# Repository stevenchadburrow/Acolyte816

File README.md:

# Acolyte816

An Acolyte Computer using the W65C816S.

It runs at 12.5 MHz and has 1 MB of RAM.  Video output of 64-colors at 320x240 or monochrome at 640x240.  PS/2 Keyboard and Mouse, 2x Genesis Controllers, and 1-Voice Square wave audio output.

This is a ROM-less design, having 512 bytes of bootloader code in the PIC16F886 "spoon feeding" the '816 on power-up or reset.  After that the PIC controls the MicroSD Card to access up to 2GB of memory.

The Simulator is powered by gianlucag's 6502 emulator library, with Agumander's W65C02 edits.  The LICENSE.txt pertains to the "mos6502-Edit816.h" and "mos6502-Edit816.cpp" files only.

BODGES REQUIRED:  The 74AHCT245 connected to the PIC needs two changes: One, Pin 1 is no longer R/W but instead connected to +5V. Two, Pin 19 is connected to RC5.  Also, the FTDI USB 6-pin connector has RTS and DTS lines cut and no longer connected to RC4 and RC5.

A picture of the board after bodges.
<kbd>

</kbd>

Splash showing 64-colors and text display together.
<kbd>

</kbd>

Bootloader fallback monitor, when SDcard is not present.
<kbd>

</kbd>

Basic system monitor for read/write/execute.
<kbd>

</kbd>

Text editor with vertical scrolling, will be used as IDE for a higher level language soon.
<kbd>

</kbd>

First game for the system: Tetra!
<kbd>

</kbd>

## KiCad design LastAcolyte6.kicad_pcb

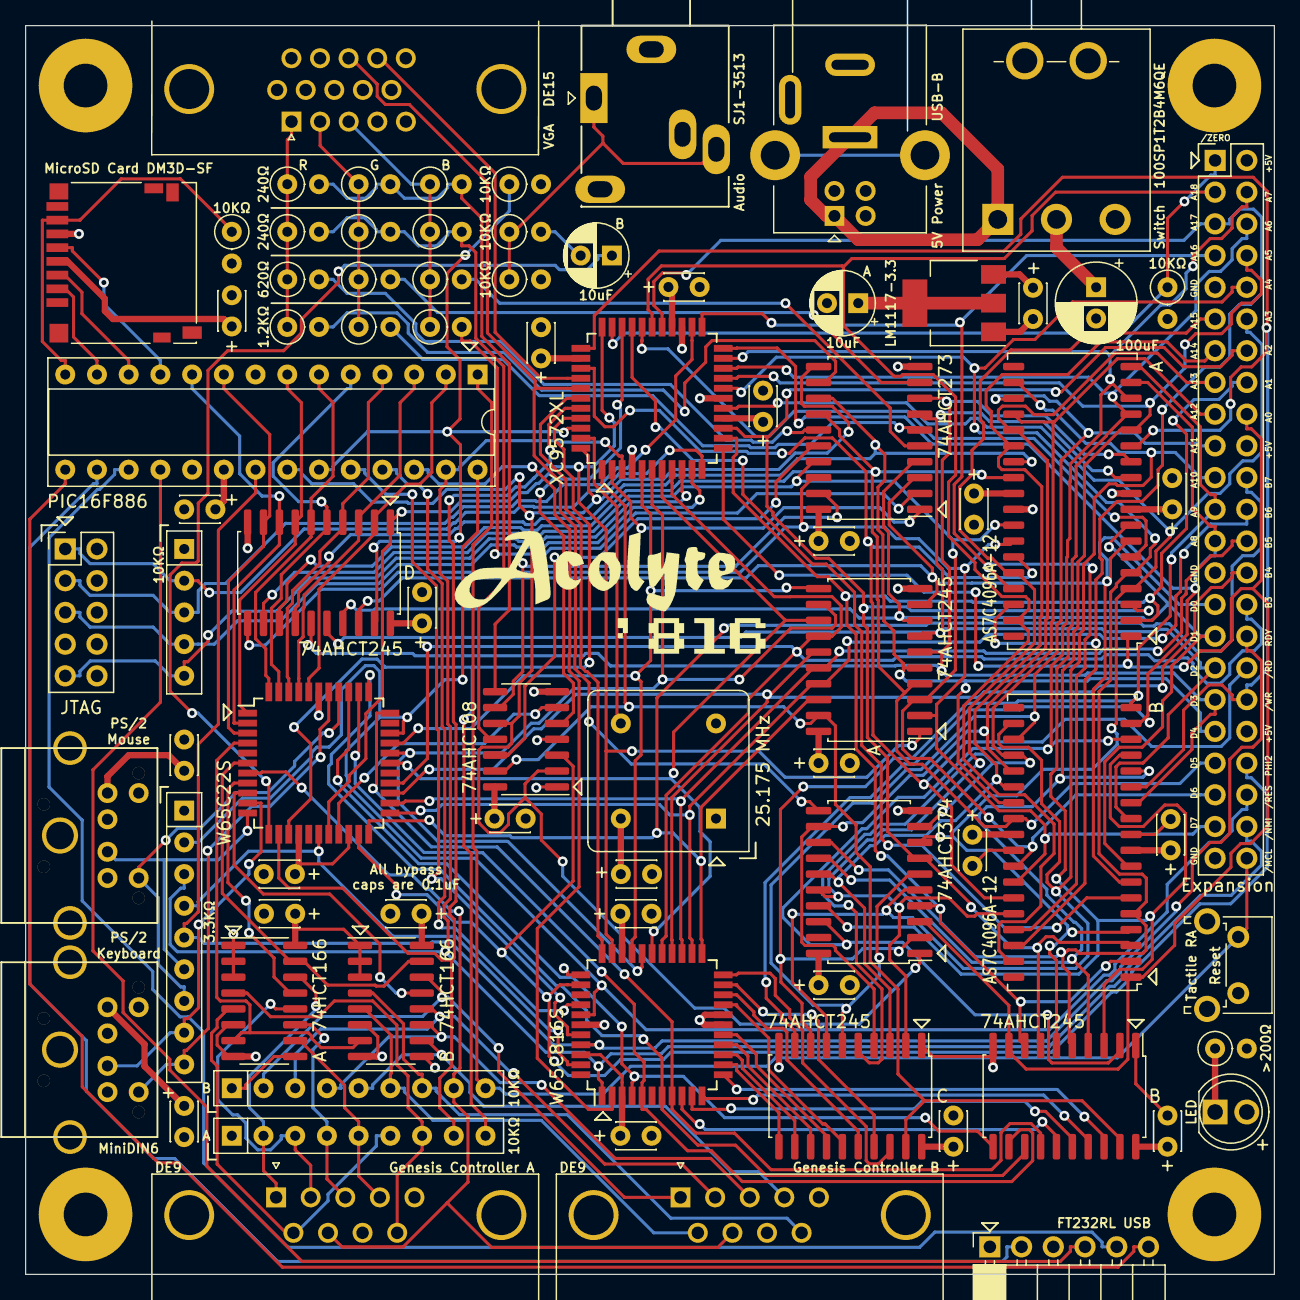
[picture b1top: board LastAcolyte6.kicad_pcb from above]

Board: 4 copper layers, 100.0 x 100.0 mm, 88 parts (1 on the bottom side), 140 nets.

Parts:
C1: C_Polarized_US; CP_Radial_D6.3mm_P2.50mm
C2, C4, C5, C6, C7, C8, C9, C10, C11, C12, C13, C14, C15, C16, C17, C18, C19, C20, C21, C23, C24, C25, C26, C27, C28: C_Small; C_Disc_D3.0mm_W2.0mm_P2.50mm
C3, C22: C_Polarized_Small_US; CP_Radial_D5.0mm_P2.50mm
D1: LED; CustomLED
G102: LOGO; Mystery
G1000: LOGO; AcolyteTitle
G1001: LOGO; Acolyte816
J1: Conn_02x23_Odd_Even; PinHeader_2x23_P2.54mm_Vertical
J2, J4: DE9_Plug; DSUB-9_Male_Horizontal_P2.77x2.84mm_EdgePinOffset7.70mm_Hou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
J3: Conn_02x05_Odd_Even; PinHeader_2x05_P2.54mm_Vertical
J5: DE15_Receptacle_HighDensity; DSUB-15-HD_Female_Horizontal_P2.29x2.54mm_VGA
J6: AudioJack3; BIGJack_3.5mm_Ledino_KB3SPRS_Horizontal
J7, J8: Mini-DIN-6; PS2_Din6
J9: Micro_SD_Card; microSD_HC_Hirose_DM3D-SF
J10: DualPower_USB_B; DualPowerSupply
J11: Conn_01x06; PinSocket_1x06_P2.54mm_Horizontal
R3, R4, R5, R7, R8, R9, R10, R11, R12, R13, R14, R15, R16, R18, R19, R20, R21, R22: R_US; R_Axial_DIN0207_L6.3mm_D2.5mm_P2.54mm_Vertical
RN1, RN2, RN3: R_Network08_US; R_Array_SIP9
RN4: R_Network04_US; R_Array_SIP5
SW1: SW_Push; SW_Tactile_SPST_Angled_PTS645Vx83-2LFS
SW2: SW_SPDT; SPDT-100SP1T2B4M6QE
TP1, TP2, TP3, TP4: TestPoint; ScrewHole-4-40
U1: XC9572VQ44; TQFP-44_10x10mm_P0.8mm
U2, U7: IS61C5128AL-10KLI; SOJ-36_10.16x23.49mm_P1.27mm
U3: LM1117MP-3.3; SOT-223-3_TabPin2
U4: W65C816SxQ; TQFP-44_10x10mm_P0.8mm
U5: W65C22SxQ; TQFP-44_10x10mm_P0.8mm
U6: 74AHCT273; SOIC-20-Adj_7.5x12.8mm_P1.27mm
U8, U9: 74HCT166; SOIC-16_3.9x9.9mm_P1.27mm
U10, U11, U15, U16: 74AHCT245; SOIC-20-Adj_7.5x12.8mm_P1.27mm
U12: 74AHCT08; SOIC-14_3.9x8.7mm_P1.27mm
U19: 74AHCT374; SOIC-20-Adj_7.5x12.8mm_P1.27mm
U21: PIC16F886-IP; DIP-28_W7.62mm_Socket
X1: CXO_DIP8; Oscillator_DIP-8

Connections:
+3.3V: C3.1, C5.2, C9.2, C13.2, C17.2, C21.2, J3.4, J9.4 (VDD), R3.2, RN4.1 (common), U1.15 (VCC-P21), U1.26 (VCCIO-P32), U1.35 (VCC-P41), U3.2 (VO), U21.20 (VDD)
+5V: C1.1, C2.2, C4.2, C6.2, C7.2, C8.2, C10.2, C11.2, C12.2, C14.2, C15.2, C16.2, C18.2, C19.2, C20.2, C23.2, C24.2, C25.2, C26.2, C27.2, C28.2, D1.2 (A), J1.2, J1.20, J1.38, J2.5, J4.5, J7.4, J8.4, RN1.1 (common), RN2.1 (common), RN3.1 (common), SW2.2 (B), U2.9 (VDD), U2.27 (VDD), U3.3 (VI), U4.3 (VDD), U4.31 (VDD), U4.34 (BE), U4.42 (~ABORT), U5.15 (VDD), U5.20 (CS1), U6.20 (VCC), U7.9 (VDD), U7.27 (VDD), U8.1 (Ds), U8.2 (A), U8.3 (B), U8.9 (Clr), U8.16 (VCC), U9.1 (Ds), U9.2 (A), U9.3 (B), U9.9 (Clr), U9.16 (VCC), U10.20 (VCC), U11.20 (VCC), U12.1, U12.4, U12.14 (VCC), U15.20 (VCC), U16.20 (VCC), U19.20 (VCC), X1.8 (Vcc)
/A0: J1.18, U1.12 (P18), U2.1 (A0), U7.1 (A0), U15.9 (A7), U19.3 (D0)
/A1: J1.16, U1.13 (P19), U2.2 (A1), U7.2 (A1), U15.8 (A6), U19.4 (D1)
/A2: J1.14, U1.14 (P20), U2.3 (A2), U7.3 (A2), U15.7 (A5), U19.7 (D2)
/A3: J1.12, U1.16 (P22), U2.4 (A3), U7.4 (A3), U15.6 (A4), U19.8 (D3)
/A4: J1.10, U1.18 (P24), U2.5 (A4), U7.5 (A4), U15.5 (A3), U19.13 (D4)
/A5: J1.8, U1.19 (P25), U2.14 (A5), U7.14 (A5), U15.4 (A2), U19.14 (D5)
/A6: J1.6, U1.20 (P26), U2.15 (A6), U7.15 (A6), U15.3 (A1), U19.17 (D6)
/A7: J1.4, U1.21 (P27), U2.16 (A7), U7.16 (A7), U15.2 (A0), U19.18 (D7)
/A8: J1.25, U1.22 (P28), U2.17 (A8), U7.17 (A8), U16.9 (A7)
/A9: J1.23, U2.18 (A9), U7.18 (A9), U16.8 (A6), U19.2 (O0)
/A10: J1.21, U2.20 (A10), U7.20 (A10), U16.7 (A5), U19.5 (O1)
/A11: J1.19, U2.21 (A11), U7.21 (A11), U16.6 (A4), U19.6 (O2)
/A12: J1.17, U2.22 (A12), U7.22 (A12), U16.5 (A3), U19.9 (O3)
/A13: J1.15, U2.23 (A13), U7.23 (A13), U16.4 (A2), U19.12 (O4)
/A14: J1.13, U2.24 (A14), U7.24 (A14), U16.3 (A1), U19.15 (O5)
/A15: J1.11, U2.32 (A15), U7.32 (A15), U16.2 (A0), U19.16 (O6)
/A16: J1.7, U1.23 (P29), U2.33 (A16), U7.33 (A16)
/A17: J1.5, U1.27 (P33), U2.34 (A17), U7.34 (A17)
/A18: J1.3, U1.28 (P34), U2.35 (A18), U7.35 (A18)
/B0: U1.5 (P11), U4.30 (D0), U5.30 (D0), U10.11 (B7)
/B1: U1.6 (P12), U4.29 (D1), U5.29 (D1), U10.12 (B6)
/B2: U1.7 (P13), U4.28 (D2), U5.28 (D2), U10.13 (B5)
/B3: J1.30, U1.8 (P14), U4.27 (D3), U5.26 (D3), U10.14 (B4)
/B4: J1.28, U4.26 (D4), U5.25 (D4), U10.15 (B3)
/B5: J1.26, U4.25 (D5), U5.24 (D5), U10.16 (B2)
/B6: J1.24, U4.24 (D6), U5.23 (D6), U10.17 (B1)
/B7: J1.22, U4.23 (D7), U5.22 (D7), U10.18 (B0)
/C0: U4.4 (A0), U5.36 (RS0), U15.11 (B7)
/C1: U4.5 (A1), U5.35 (RS1), U15.12 (B6)
/C2: U4.7 (A2), U5.34 (RS2), U15.13 (B5)
/C3: U4.8 (A3), U5.33 (RS3), U15.14 (B4)
/C4: U4.9 (A4), U15.15 (B3)
/C5: U4.10 (A5), U15.16 (B2)
/C6: U4.11 (A6), U15.17 (B1)
/C7: U4.12 (A7), U15.18 (B0)
/C8: U4.13 (A8), U16.11 (B7)
/C9: U4.14 (A9), U16.12 (B6)
/C10: U4.15 (A10), U16.13 (B5)
/C11: U4.16 (A11), U16.14 (B4)
/C12: U4.19 (A12), U16.15 (B3)
/C13: U4.20 (A13), U16.16 (B2)
/C14: U4.21 (A14), U16.17 (B1)
/C15: U4.22 (A15), U16.18 (B0)
/D0: J1.29, U2.7 (I/O0), U6.3 (D0), U7.7 (I/O0), U10.9 (A7), U11.18 (B0)
/D1: J1.31, U2.8 (I/O1), U6.4 (D1), U7.8 (I/O1), U10.8 (A6), U11.17 (B1)
/D2: J1.33, U2.11 (I/O2), U6.7 (D2), U7.11 (I/O2), U10.7 (A5), U11.16 (B2)
/D3: J1.35, U2.12 (I/O3), U6.8 (D3), U7.12 (I/O3), U10.6 (A4), U11.15 (B3)
/D4: J1.37, U2.25 (I/O4), U6.13 (D4), U7.25 (I/O4), U10.5 (A3), U11.14 (B4)
/D5: J1.39, U2.26 (I/O5), U6.14 (D5), U7.26 (I/O5), U10.4 (A2), U11.13 (B5)
/D6: J1.41, U2.29 (I/O6), U6.17 (D6), U7.29 (I/O6), U10.3 (A1), U11.12 (B6)
/D7: J1.43, U2.30 (I/O7), U6.18 (D7), U7.30 (I/O7), U10.2 (A0), U11.11 (B7)
/E0: U5.40 (PA0), U11.2 (A0), U21.2 (ULPWU/C12IN0-/AN0/RA0)
/E1: U5.41 (PA1), U11.3 (A1), U21.3 (C12IN1-/AN1/RA1)
/E2: U5.42 (PA2), U11.4 (A2), U21.4 (CVref/C2IN1+/Vref-/AN2/RA2)
/E3: U5.43 (PA3), U11.5 (A3), U21.5 (C1IN+/Vref+/AN3/RA3)
/E4: U5.44 (PA4), U11.6 (A4), U21.6 (T0CKI/C1OUT/RA4)
/E5: U5.1 (PA5), U11.7 (A5), U21.7 (~SS/C2OUT/AN4/RA5)
/E6: U5.2 (PA6), U11.8 (A6), U21.10 (CLKOUT/OSC2/RA6)
/E7: U5.3 (PA7), U11.9 (A7), U21.9 (CLKIN/OSC1/RA7)
AUDIO-NEG: C22.2, R14.2
AUDIO-OUT: J6.R, J6.T, R14.1, R16.1
AUDIO-SOURCE: C22.1, U5.12 (PB7)
BLUE: J5.3, R12.1, R13.1, R19.1, R22.1
BLUE-PIX-A: R12.2, U6.5 (Q1)
BLUE-PIX-B: R13.2, U6.2 (Q0)
DSR: J11.6, U21.15 (RC4/SDI/SDA)
EMU: U1.39 (P1), U4.33 (E)
GND: C1.2, C2.1, C3.2, C4.1, C5.1, C6.1, C7.1, C8.1, C9.1, C10.1, C11.1, C12.1, C13.1, C14.1, C15.1, C16.1, C17.1, C18.1, C19.1, C20.1, C21.1, C23.1, C24.1, C25.1, C26.1, C27.1, C28.1, J1.9, J1.27, J1.45, J2.8, J3.2, J3.10, J4.8, J5.5, J5.6, J5.7, J5.8, J5.10, J6.S, J7.3, J8.3, J9.6 (VSS), J10.4 (GND), J10.7, J11.1, R4.2, R5.2, R7.2, R16.2, SW1.2, TP1.1, TP2.1, TP3.1, TP4.1, U1.4 (GND-P10), U1.17 (GND-P23), U1.25 (GND-P31), U2.10 (GND), U2.28 (GND), U3.1 (GND), U4.17 (VSS), U4.18 (VSS), U4.39 (VSS), U5.39 (VSS), U6.10 (GND), U7.10 (GND), U7.28 (GND), U8.6 (CE), U8.8 (GND), U9.6 (CE), U9.8 (GND), U10.10 (GND), U11.10 (GND), U12.7 (GND), U15.1 (A->B), U15.10 (GND), U16.1 (A->B), U16.10 (GND), U19.10 (GND), U21.8 (VSS), U21.19 (VSS), X1.4 (GND)
GREEN: J5.2, R10.1, R11.1, R18.1, R21.1
GREEN-PIX-A: R10.2, U6.9 (Q3)
GREEN-PIX-B: R11.2, U6.6 (Q2)
H-SYNC: J5.13, U1.38 (P44), U19.11 (Cp)
JOY-BUTTON1-A: J2.6, RN1.6 (R5), U8.5 (D)
JOY-BUTTON1-B: J4.6, RN2.6 (R5), U9.5 (D)
JOY-BUTTON2-A: J2.9, RN1.7 (R6), U8.4 (C)
JOY-BUTTON2-B: J4.9, RN2.7 (R6), U9.4 (C)
JOY-CLOCK: U5.4 (PB0), U8.7 (Clk), U9.7 (Clk)
JOY-DATA-A: U5.8 (PB3), U8.13 (Qh)
JOY-DATA-B: U5.9 (PB4), U9.13 (Qh)
JOY-DOWN-A: J2.2, RN1.3 (R2), U8.12 (G)
JOY-DOWN-B: J4.2, RN2.3 (R2), U9.12 (G)
JOY-LATCH: U5.6 (PB1), U8.15 (PE), U9.15 (PE)
JOY-LEFT-A: J2.3, RN1.4 (R3), U8.11 (F)
JOY-LEFT-B: J4.3, RN2.4 (R3), U9.11 (F)
JOY-RIGHT-A: J2.4, RN1.5 (R4), U8.10 (E)
JOY-RIGHT-B: J4.4, RN2.5 (R4), U9.10 (E)
JOY-SELECT: J2.7, J4.7, RN2.8 (R7), U5.7 (PB2)
JOY-UP-A: J2.1, RN1.2 (R1), U8.14 (H)
JOY-UP-B: J4.1, RN2.2 (R1), U9.14 (H)
JTAG-TCK: J3.1, RN4.2 (R1), U1.11 (TCK-P17)
JTAG-TDI: J3.9, RN4.5 (R4), U1.9 (TDI-P15)
JTAG-TDO: J3.3, RN4.3 (R2), U1.24 (TDO-P30)
JTAG-TMS: J3.5, RN4.4 (R3), U1.10 (TMS-P16)
KEY-CLOCK: J7.5, RN3.9 (R8), U5.38 (CA1)
KEY-DATA: J7.1, RN3.8 (R7), U5.10 (PB5)
LED: D1.1 (K), R7.1
MCLK: U1.43 (P5-GCK1), X1.5 (OUT)
MOUSE-CLOCK: J8.5, RN3.7 (R6), U5.37 (CA2)
MOUSE-DATA: J8.1, RN3.6 (R5), U5.11 (PB6)
PHI2: J1.40, U4.35 (ϕ0), U5.21 (ϕ2), U12.3
PHI2-3V3: U1.44 (P6-GCK2), U6.11 (Cp), U12.2, U12.10, U19.1 (OE), U21.22 (P1C/AN10/RB1)
POWER: J10.1 (VBUS), J10.6, SW2.1 (A)
RDY: J1.32, RN3.5 (R4), U4.41 (RDY), U21.21 (INT/AN12/RB0)
RED: J5.1, R8.1, R9.1, R15.1, R20.1
RED-PIX-A: R8.2, U6.15 (Q5)
RED-PIX-B: R9.2, U6.12 (Q4)
RTS: J11.2, U21.16 (RC5/SDO)
RX/DT: J11.4, U21.18 (RC7/RX/DT)
SHIFT-CLOCK: RN1.8 (R7), U1.40 (P2), U5.13 (CB1)
SHIFT-DATA: RN1.9 (R8), U1.41 (P3), U5.14 (CB2)
SPI-CLK: J9.5 (CLK), U21.11 (RC0/T1OSO/T1CK1)
SPI-CS: J9.2 (DAT3/CD), U21.13 (RC2/P1A/CCP1)
SPI-MISO: J9.7 (DAT0), R3.1, U21.14 (RC3/SCK/SCL)
SPI-MOSI: J9.3 (CMD), U21.12 (RC1/T1OSI/CCP2)
TEXT-PIX-A: U6.19 (Q7), U12.9
TEXT-PIX-B: U6.16 (Q6), U12.12
TX/CK: J11.5, U21.17 (RC6/TX/CK)
V-SYNC: J5.14, U1.37 (P43)
VDA: U4.37 (VDA), U21.25 (P1D/AN11/RB4)
VISIBLE: U1.2 (P8), U6.1 (~Mr)
VPA: U4.2 (VPA), U21.26 (~T1G/AN13/RB5)
WHITE-PIX-A: R15.2, R18.2, R19.2, U12.8
WHITE-PIX-B: R20.2, R21.2, R22.2, U12.11
~BOOT: R5.1, U1.42 (P4), U11.19 (CE), U21.23 (P1B/AN8/RB2)
~IRQ: RN3.4 (R3), U4.43 (~IRQ), U5.17 (~IRQ)
~MCLR: J1.46, RN2.9 (R8), SW1.1, U21.1 (RE3/~MCLR/Vpp)
~NMI: J1.44, RN3.3 (R2), U1.3 (P9), U4.1 (~NMI), U21.27 (ICSPCLK/RB6)
~PHI2-3V3: U1.1 (P7-GCK3), U10.19 (CE), U12.13, U15.19 (CE), U16.19 (CE)
~RAM-A: U1.29 (P35), U7.6 (~CE)
~RAM-B: U1.30 (P36), U2.6 (~CE)
~RD: J1.34, U1.36 (P42-GTS1), U2.31 (~OE), U7.31 (~OE)
~RES: J1.42, RN3.2 (R1), U4.38 (~RES), U5.31 (~RES), U21.28 (ICSPDAT/RB7)
~RW: U1.33 (P39-GSR), U4.32 (R/~W), U5.18 (R/~W), U10.1 (A->B), U11.1 (A->B)
~VIA-3V3: U1.31 (P37), U12.5
~VIA: U5.19 (~CS2), U12.6
~VP: U4.40 (~VP), U21.24 (PGM/C12IN2-/AN8/RB3)
~WR: J1.36, U1.34 (P40-GTS2), U2.13 (~WE), U7.13 (~WE)
~ZERO: J1.1, R4.1, U1.32 (P38)

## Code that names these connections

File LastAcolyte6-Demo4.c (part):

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/*
The boot sequence is as follows:
	Bring /RES low and gain control of PHI2.
	Release /RES to be pulled high, start single stepping CPU.
	When /VP goes low, send $0000 reset vector (arbitrary).
	Send LDA# and STAal instructions, filling $FE00-$FFFF with boot code.
	If SDcard is ready, send 128KB of data as well.
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	//for (unsigned int i=0; i<1000; i++) { }

	// assumes PHI2 is low already
	RB1 = 1; // bring PHI2 high

	// delay needed?
	//for (unsigned int i=0; i<1000; i++) { }

	RB1 = 0; // bring PHI2 low
}

void serial_initialize(void)
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
void nmi_ground(void)
{
	RB6 = 0; // get /NMI ready for low
	TRISB = TRISB & 0xBF; // /NMI is output
}

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// This was used for the Arduino, but has been modified to work here.
void sdcard_enable(void)
{
	RC2 = 0; // CS is low
}

void sdcard_disable(void)
{
	RC2 = 1; // CS is high
}

void sdcard_longdelay(void)
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
void sdcard_toggle(void)
{
	RC0 = 1; // CLK goes high then low again
	RC0 = 0; // make as fast as possible, use asm{ ... } ?
}

void sdcard_sendbyte(unsigned char value)
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	{
		if (temp_value >= 0x80)
		{
			RC1 = 1; // MOSI is high
		}
		else
		{
			RC1 = 0; // MOSI is low
		}

		temp_value = temp_value << 1;
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
void sdcard_pump(void)
{
	RC2 = 1; // CS is high, must disable the device
	RC1 = 1; // MOSI is high, AND leave mosi high!!!

	sdcard_longdelay();

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
	TRISC = (TRISC & 0xF0) | 0x08;

	RC2 = 1; // CS is high
	RC1 = 1; // MOSI is high
	RC0 = 0; // CLK is low

	sdcard_disable();
	sdcard_pump();
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	PORTA = bank; // bank addr
	toggle();

	RC5 = 1; // shut down transceiver

	//TRISA = 0xFF; // data

	toggle();

	RC5 = 0; // start up transceiver

	//TRISA = 0x00;
}
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
	//TRISA = 0xFF; // release data bus

	RC5 = 1; // shut down transceiver

	RB7 = 0; // get /RES ready for low
	TRISB = 0x7B; // /RES is output

	for (unsigned char i=0; i<32; i++) // cycle phi2 32 times while /RES is low
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
	TRISB = 0xFB; // release PHI2

	RB2 = 1; // have /BOOT go high, letting CPLD run normally

	serial_transmitchar('*');

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
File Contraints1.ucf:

NET emu LOC = P39;

NET shift_clock LOC = P40;
NET shift_data LOC = P41;

NET boot LOC = P42;

NET master_clock LOC = P43;
NET phi2 LOC = P44;
NET not_phi2 LOC = P1;

NET visible LOC = P2;
NET nmi LOC = P3;

NET ram_a LOC = P29;
NET ram_b LOC = P30;
NET via LOC = P31;

NET zero LOC = P32;

NET rw LOC = P33;
NET wr LOC = P34;
NET rd LOC = P36;

NET vsync LOC = P37;
NET hsync LOC = P38;

NET bank[0] LOC = P5;
NET bank[1] LOC = P6;
NET bank[2] LOC = P7;
NET bank[3] LOC = P8;

NET address[0] LOC = P12;
NET address[1] LOC = P13;
NET address[2] LOC = P14;
NET address[3] LOC = P16;

NET address[4] LOC = P18;
NET address[5] LOC = P19;
NET address[6] LOC = P20;
NET address[7] LOC = P21;

NET address[8] LOC = P22;

NET top[0] LOC = P23;
NET top[1] LOC = P27;
NET top[2] LOC = P28;

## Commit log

2024-01-21 Rename Acolyte816-Routed.png to OLD/Acolyte816-Routed.png
2024-01-21 Rename AcolyteAssembler.cpp to OLD/AcolyteAssembler.cpp
2024-01-21 Rename AcolyteSimulator.cpp to OLD/AcolyteSimulator.cpp
2024-01-21 Rename LastAcolyte6-Bootloader.asm to OLD/LastAcolyte6-Bootloader.asm
2024-01-21 Rename LastAcolyte6-Bootloader.bin to OLD/LastAcolyte6-Bootloader.bin
2024-01-21 Rename LastAcolyte6-Demo-1-9-24.asm to OLD/LastAcolyte6-Demo-1-9-24.asm
2024-01-21 Rename LastAcolyte6-Demo-1-9-24.bin to OLD/LastAcolyte6-Demo-1-9-24.bin
2024-01-21 Rename LastAcolyte6-Demo.asm to OLD/LastAcolyte6-Demo.asm
2024-01-21 Rename LastAcolyte6-Demo.bin to OLD/LastAcolyte6-Demo.bin
2024-01-21 Rename LastAcolyte6-Gerbers.zip to OLD/LastAcolyte6-Gerbers.zip
2024-01-21 Rename LastAcolyte6.c to OLD/LastAcolyte6.c
2024-01-21 Rename LastAcolyte6.hex to OLD/LastAcolyte6.hex
2024-01-21 Rename Mouser_BOM.xls to OLD/Mouser_BOM.xls
2024-01-21 Rename Simulator-Bootloader.png to OLD/Simulator-Bootloader.png
2024-01-21 Rename Simulator-Demo.png to OLD/Simulator-Demo.png
2024-01-21 Rename Simulator-Scratch.png to OLD/Simulator-Scratch.png
2024-01-21 Rename Simulator-Splash.png to OLD/Simulator-Splash.png
2024-01-21 Rename Simulator-Tetra.png to OLD/Simulator-Tetra.png
2024-01-21 Rename Verilog4.jed to OLD/Verilog4.jed
2024-01-21 Rename Verilog4.v to OLD/Verilog4.v
2024-01-21 Rename 20240118_165125.jpg to Board.jpg
2024-01-21 Rename 20240121_122507.jpg to Picture-Splash.jpg
2024-01-21 Rename 20240121_122657.jpg to Picture-Monitor.jpg
2024-01-21 Rename 20240121_122928.jpg to Picture-Editor.jpg
2024-01-21 Rename 20240121_123018.jpg to Picture-Tetra.jpg
2024-01-21 Rename 20240118_165416.jpg to Picture-Fallback.jpg
